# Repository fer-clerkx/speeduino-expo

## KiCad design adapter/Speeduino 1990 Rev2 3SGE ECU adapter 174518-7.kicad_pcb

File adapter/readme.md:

64 pin for NA Toyota MR2 SW20 (1992)

# [For sale here](https://www.tindie.com/products/russian/ecu-64p-connector-bare-pcb-honda-miata-nanb1/)

[Forum thread](https://rusefi.com/forum/viewtopic.php?f=4&t=507)

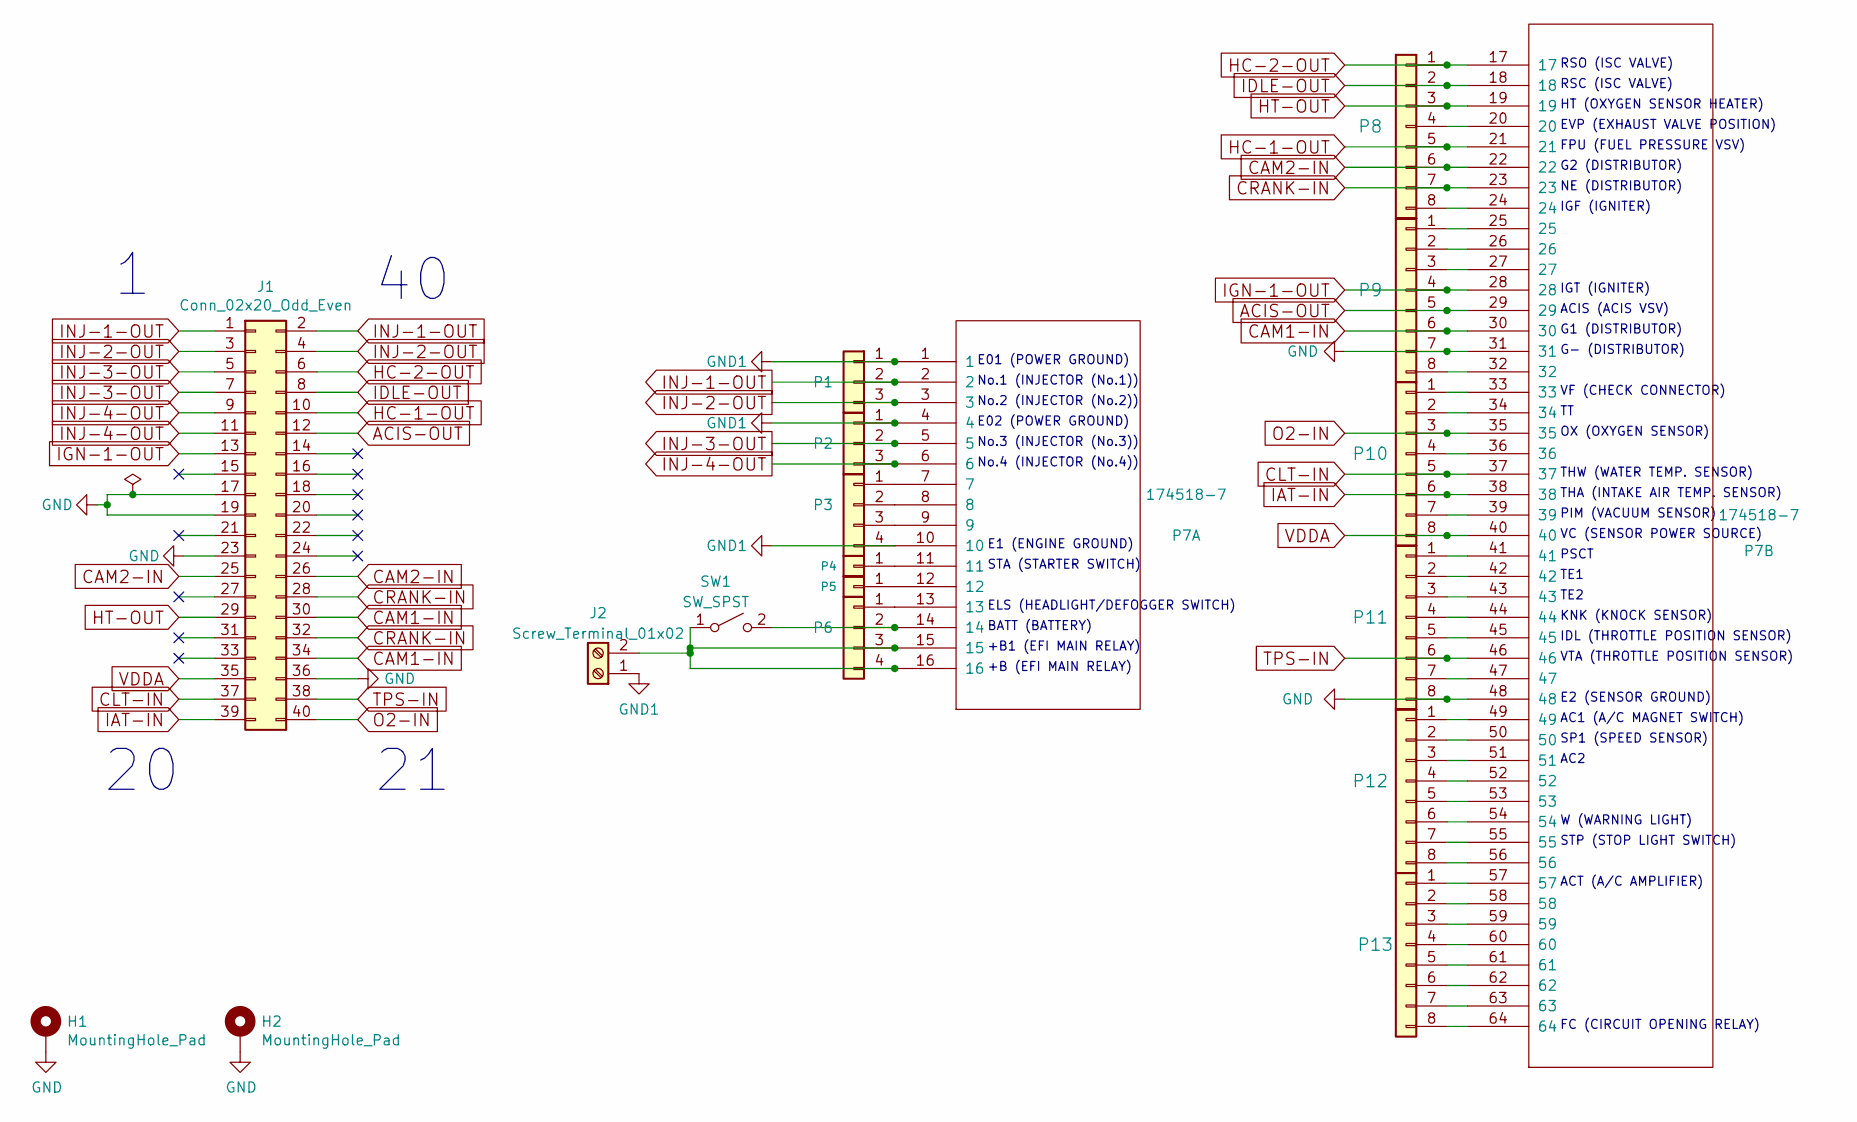
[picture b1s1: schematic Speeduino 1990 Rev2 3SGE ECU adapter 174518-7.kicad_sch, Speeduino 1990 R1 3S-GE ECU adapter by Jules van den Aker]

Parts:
H1, H2: MountingHole_Pad; MountingHole_3.2mm_M3_Pad_Via
J1: Conn_02x20_Odd_Even; IDC-Header_2x20_P2.54mm_Vertical
J2: Screw_Terminal_01x02; TerminalBlock_Phoenix_MKDS-1,5-2_1x02_P5.00mm_Horizontal
P1, P2: CONN_3; PinHeader_1x03_P2.54mm_Vertical
P3, P6: Conn_01x04_Male; PinHeader_2x02_P2.54mm_Vertical
P4, P5: CONN_1; PinHeader_1x01_P2.54mm_Vertical
P7: 174518-7
P8, P9, P10, P11, P12, P13: CONN_8; PinHeader_1x08_P2.54mm_Vertical
SW1: SW_SPST; SolderJumper-2_P1.3mm_Bridged_Pad1.0x1.5mm

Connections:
ACIS-OUT: J1.12, P7.29, P9.5
CAM1-IN: J1.30, J1.34, P7.30, P9.6
CAM2-IN: J1.25, J1.26, P7.22, P8.6
CLT-IN: J1.37, P7.37, P10.5
CRANK-IN: J1.28, J1.32, P7.23, P8.7
GND: H1.1, H2.1, J1.17, J1.19, J1.23, J1.36, P7.31, P7.48, P9.7, P11.8
GND1: J2.1, P1.1, P2.1, P3.4, P7.1, P7.4, P7.10
HC-1-OUT: J1.10, P7.21, P8.5
HC-2-OUT: J1.6, P7.17, P8.1
HT-OUT: J1.29, P7.19, P8.3
IAT-IN: J1.39, P7.38, P10.6
IDLE-OUT: J1.8, P7.18, P8.2
IGN-1-OUT: J1.13, P7.28, P9.4
INJ-1-OUT: J1.1, J1.2, P1.2, P7.2
INJ-2-OUT: J1.3, J1.4, P1.3, P7.3
INJ-3-OUT: J1.5, J1.7, P2.2, P7.5
INJ-4-OUT: J1.9, J1.11, P2.3, P7.6
unnamed: J2.2, P6.3, P6.4, P7.15, P7.16, SW1.1 (A)
unnamed: P3.1, P7.7
unnamed: P3.2, P7.8
unnamed: P3.3, P7.9
unnamed: P4.1, P7.11
unnamed: P5.1, P7.12
unnamed: P6.1, P7.13
unnamed: P6.2, P7.14, SW1.2 (B)
unnamed: P7.20, P8.4
unnamed: P7.24, P8.8
unnamed: P7.25, P9.1
unnamed: P7.26, P9.2
unnamed: P7.27, P9.3
unnamed: P7.32, P9.8
unnamed: P7.33, P10.1
unnamed: P7.34, P10.2
unnamed: P7.36, P10.4
unnamed: P7.39, P10.7
unnamed: P7.41, P11.1
unnamed: P7.42, P11.2
unnamed: P7.43, P11.3
unnamed: P7.44, P11.4
unnamed: P7.45, P11.5
unnamed: P7.47, P11.7
unnamed: P7.49, P12.1
unnamed: P7.50, P12.2
unnamed: P7.51, P12.3
unnamed: P7.52, P12.4
unnamed: P7.53, P12.5
unnamed: P7.54, P12.6
unnamed: P7.55, P12.7
unnamed: P7.56, P12.8
unnamed: P7.57, P13.1
unnamed: P7.58, P13.2
unnamed: P7.59, P13.3
unnamed: P7.60, P13.4
unnamed: P7.61, P13.5
unnamed: P7.62, P13.6
unnamed: P7.63, P13.7
unnamed: P7.64, P13.8
O2-IN: J1.40, P7.35, P10.3
TPS-IN: J1.38, P7.46, P11.6
VDDA: J1.35, P7.40, P10.8

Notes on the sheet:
IGT (IGNITER)
W (WARNING LIGHT)
E02 (POWER GROUND)
No.4 (INJECTOR (No.4))
G1 (DISTRIBUTOR)
No.2 (INJECTOR (No.2))
KNK (KNOCK SENSOR)
NE (DISTRIBUTOR)
STA (STARTER SWITCH)
FPU (FUEL PRESSURE VSV)
AC2
ACT (A/C AMPLIFIER)
+B1 (EFI MAIN RELAY)
RSO (ISC VALVE)
ELS (HEADLIGHT/DEFOGGER SWITCH)
G- (DISTRIBUTOR)
THA (INTAKE AIR TEMP. SENSOR)
No.3 (INJECTOR (No.3))
TE2
RSC (ISC VALVE)
VF (CHECK CONNECTOR)
HT (OXYGEN SENSOR HEATER)
TE1
THW (WATER TEMP. SENSOR)
+B (EFI MAIN RELAY)
E01 (POWER GROUND)
IGF (IGNITER)
OX (OXYGEN SENSOR)
G2 (DISTRIBUTOR)
No.1 (INJECTOR (No.1))
PSCT
FC (CIRCUIT OPENING RELAY)
VTA (THROTTLE POSITION SENSOR)
E2 (SENSOR GROUND)
VC (SENSOR POWER SOURCE)
SP1 (SPEED SENSOR)
ACIS (ACIS VSV)
AC1 (A/C MAGNET SWITCH)
IDL (THROTTLE POSITION SENSOR)
STP (STOP LIGHT SWITCH)

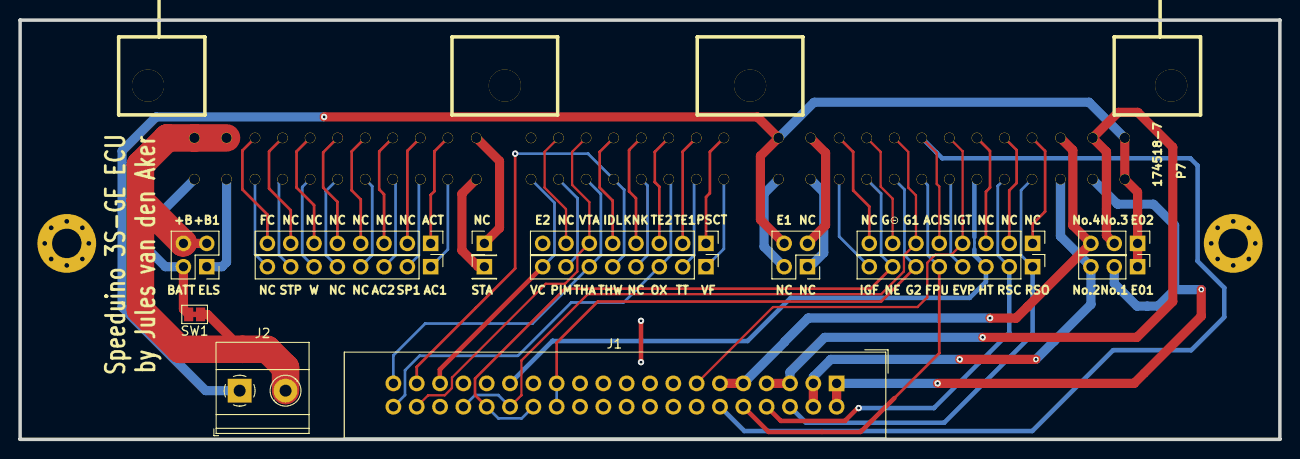
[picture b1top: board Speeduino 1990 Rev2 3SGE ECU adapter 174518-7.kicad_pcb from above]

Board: 2 copper layers, 137.2 x 45.6 mm, 18 parts (0 on the bottom side), 60 nets.

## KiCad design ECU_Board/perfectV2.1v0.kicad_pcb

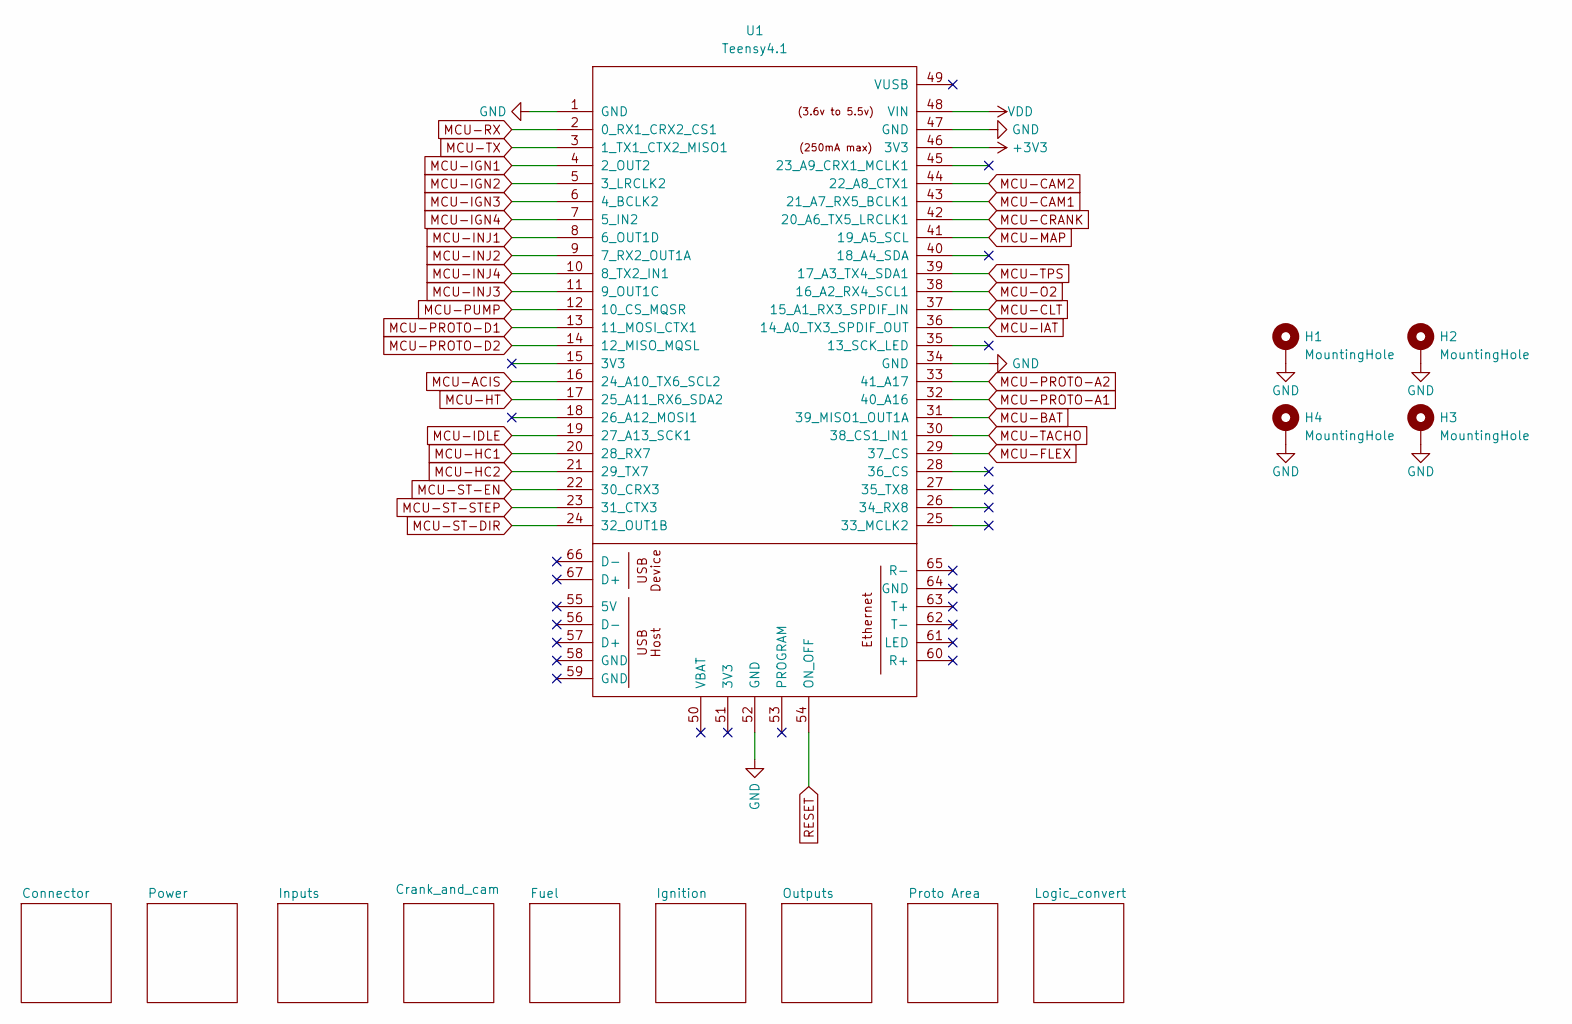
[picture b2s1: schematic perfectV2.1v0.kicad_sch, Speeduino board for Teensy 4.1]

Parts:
H1, H2, H3, H4: MountingHole; MountingHole_4.3mm_M4_Pad
U1: Teensy4.1; Teensy41

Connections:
+3V3: U1.46 (3V3); also elsewhere on the board
GND: H1.1, H2.1, H3.1, H4.1, U1.1 (GND), U1.34 (GND), U1.47 (GND), U1.52 (GND); also elsewhere on the board
MCU-ACIS: U1.16 (24_A10_TX6_SCL2); also elsewhere on the board
MCU-BAT: U1.31 (39_MISO1_OUT1A); also elsewhere on the board
MCU-CAM1: U1.43 (21_A7_RX5_BCLK1); also elsewhere on the board
MCU-CAM2: U1.44 (22_A8_CTX1); also elsewhere on the board
MCU-CLT: U1.37 (15_A1_RX3_SPDIF_IN); also elsewhere on the board
MCU-CRANK: U1.42 (20_A6_TX5_LRCLK1); also elsewhere on the board
MCU-FLEX: U1.29 (37_CS); also elsewhere on the board
MCU-HC1: U1.20 (28_RX7); also elsewhere on the board
MCU-HC2: U1.21 (29_TX7); also elsewhere on the board
MCU-HT: U1.17 (25_A11_RX6_SDA2); also elsewhere on the board
MCU-IAT: U1.36 (14_A0_TX3_SPDIF_OUT); also elsewhere on the board
MCU-IDLE: U1.19 (27_A13_SCK1); also elsewhere on the board
MCU-IGN1: U1.4 (2_OUT2); also elsewhere on the board
MCU-IGN2: U1.5 (3_LRCLK2); also elsewhere on the board
MCU-IGN3: U1.6 (4_BCLK2); also elsewhere on the board
MCU-IGN4: U1.7 (5_IN2); also elsewhere on the board
MCU-INJ1: U1.8 (6_OUT1D); also elsewhere on the board
MCU-INJ2: U1.9 (7_RX2_OUT1A); also elsewhere on the board
MCU-INJ3: U1.11 (9_OUT1C); also elsewhere on the board
MCU-INJ4: U1.10 (8_TX2_IN1); also elsewhere on the board
MCU-MAP: U1.41 (19_A5_SCL); also elsewhere on the board
MCU-O2: U1.38 (16_A2_RX4_SCL1); also elsewhere on the board
MCU-PROTO-A1: U1.32 (40_A16); also elsewhere on the board
MCU-PROTO-A2: U1.33 (41_A17); also elsewhere on the board
MCU-PROTO-D1: U1.13 (11_MOSI_CTX1); also elsewhere on the board
MCU-PROTO-D2: U1.14 (12_MISO_MQSL); also elsewhere on the board
MCU-PUMP: U1.12 (10_CS_MQSR); also elsewhere on the board
MCU-RX: U1.2 (0_RX1_CRX2_CS1); also elsewhere on the board
MCU-ST-DIR: U1.24 (32_OUT1B); also elsewhere on the board
MCU-ST-EN: U1.22 (30_CRX3); also elsewhere on the board
MCU-ST-STEP: U1.23 (31_CTX3); also elsewhere on the board
MCU-TACHO: U1.30 (38_CS1_IN1); also elsewhere on the board
MCU-TPS: U1.39 (17_A3_TX4_SDA1); also elsewhere on the board
MCU-TX: U1.3 (1_TX1_CTX2_MISO1); also elsewhere on the board
RESET: U1.54 (ON_OFF); also elsewhere on the board
VDD: U1.48 (VIN); also elsewhere on the board

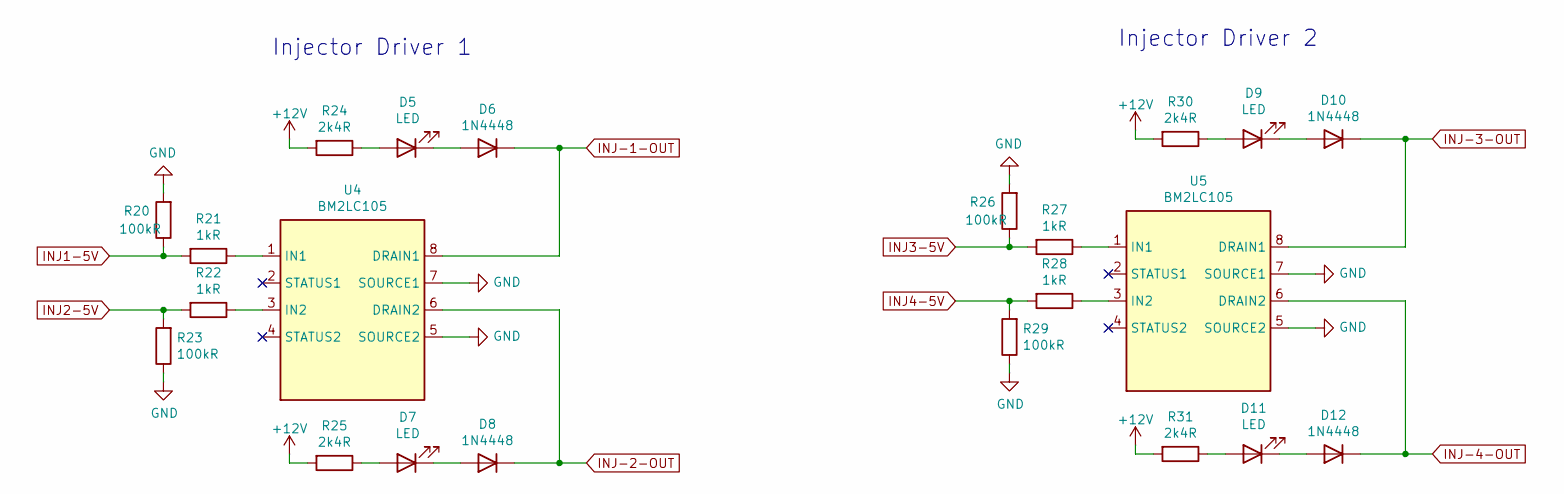
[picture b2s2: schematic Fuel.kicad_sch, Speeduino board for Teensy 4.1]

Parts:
D5, D7, D9, D11: LED; LED_0805_2012Metric; Manufacturer_Part_Number MP008293; Digikey Part Number 3796325
D6, D8, D10, D12: 1N4448; D_SOD-123; Manufacturer_Part_Number 1N4448W-7-F; Digikey Part Number 1843738
R20, R23, R26, R29: 100kR; R_0402_1005Metric; Manufacturer_Part_Number WF04P1003FTL; Digikey Part Number 2502803
R21, R22, R27, R28: 1kR; R_0402_1005Metric; Manufacturer_Part_Number WF04P1001FTL; Digikey Part Number 2502798
R24, R25, R30, R31: 2k4R; R_0805_2012Metric; Manufacturer_Part_Number MCWR08X2401FTL; Digikey Part Number 2447625
U4, U5: BM2LC105; SOP-8_3.9x4.9mm_P1.27mm; Manufacturer_Part_Number BM2LC105FJ-CE2; Digikey Part Number BM2LC105FJ-CE2CT-ND

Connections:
+12V: R24.2, R25.2, R30.2, R31.2; also elsewhere on the board
GND: R20.2, R23.1, R26.2, R29.1, U4.5 (SOURCE2), U4.7 (SOURCE1), U5.5 (SOURCE2), U5.7 (SOURCE1); also elsewhere on the board
INJ1-5V: R20.1, R21.2; also elsewhere on the board
INJ2-5V: R22.2, R23.2; also elsewhere on the board
INJ3-5V: R26.1, R27.2; also elsewhere on the board
INJ4-5V: R28.2, R29.2; also elsewhere on the board
INJ-1-OUT: D6.1 (K), U4.8 (DRAIN1); also elsewhere on the board
INJ-2-OUT: D8.1 (K), U4.6 (DRAIN2); also elsewhere on the board
INJ-3-OUT: D10.1 (K), U5.8 (DRAIN1); also elsewhere on the board
INJ-4-OUT: D12.1 (K), U5.6 (DRAIN2); also elsewhere on the board
unnamed: D5.1 (K), D6.2 (A)
unnamed: D5.2 (A), R24.1
unnamed: D7.1 (K), D8.2 (A)
unnamed: D7.2 (A), R25.1
unnamed: D9.2 (A), R30.1
unnamed: D9.1 (K), D10.2 (A)
unnamed: D11.1 (K), D12.2 (A)
unnamed: D11.2 (A), R31.1
unnamed: R21.1, U4.1 (IN1)
unnamed: R22.1, U4.3 (IN2)
unnamed: R27.1, U5.1 (IN1)
unnamed: R28.1, U5.3 (IN2)

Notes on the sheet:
Injector Driver 2
Injector Driver 1

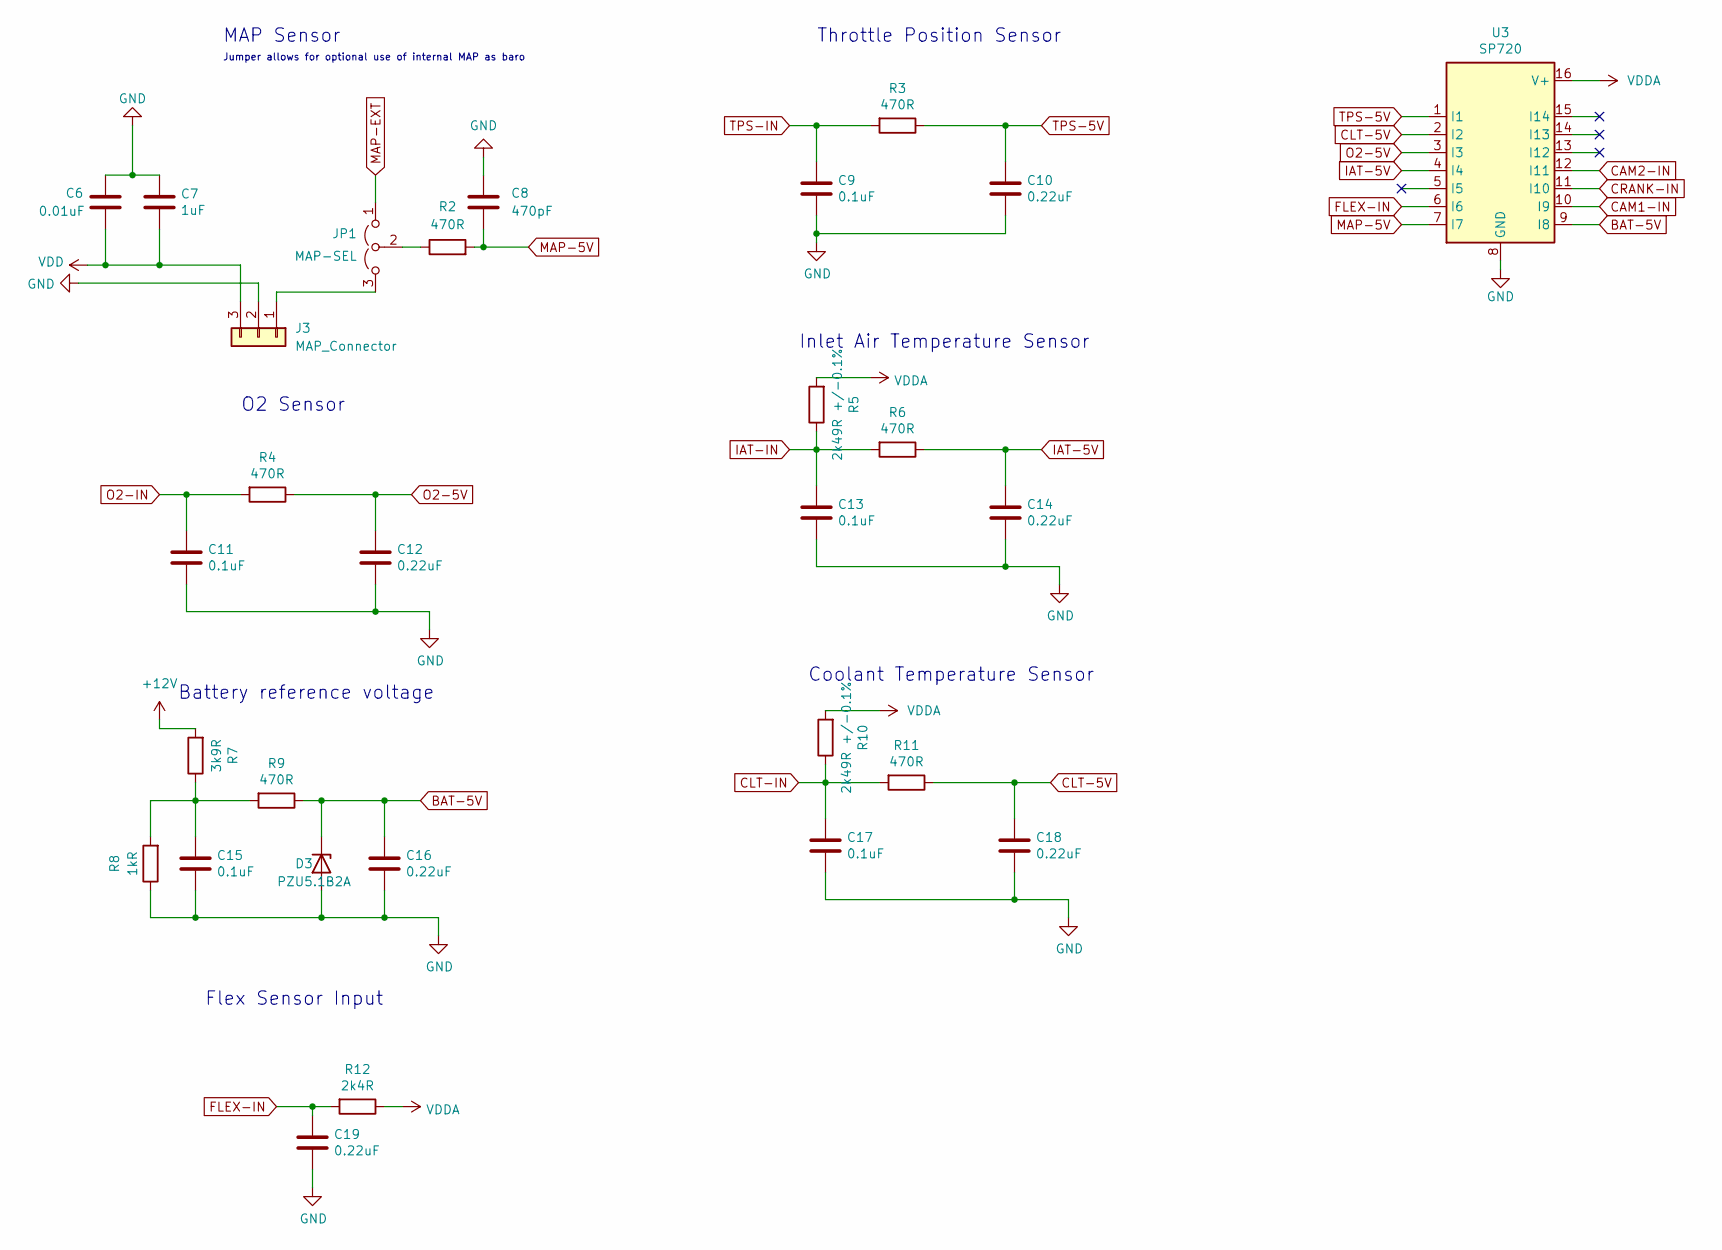
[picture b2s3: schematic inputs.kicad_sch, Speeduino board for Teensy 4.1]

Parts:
C6: 0.01uF; C_0805_2012Metric; Manufacturer_Part_Number CC0805KRX7R9BB103; Digikey Part Number 3019937
C7: 1uF; C_0805_2012Metric; Manufacturer_Part_Number CC0805KKX7R7BB105; Digikey Part Number 3369302
C8: 470pF; C_0805_2012Metric; Manufacturer_Part_Number MC0805B471K500CT; Digikey Part Number 1759216
C9, C11, C13, C15, C17: 0.1uF; C_0805_2012Metric; Manufacturer_Part_Number VJ0805Y104KXAPW1BC; Digikey Part Number 3296136
C10, C12, C14, C16, C18, C19: 0.22uF; C_0805_2012Metric; Manufacturer_Part_Number 0805B224M160CP; Digikey Part Number 3881054
D3: PZU5.1B2A; D_SOD-323; Manufacturer_Part_Number PZU5.1B2A-QX; Digikey Part Number 4126444
J3: MAP_Connector; PinSocket_1x03_P2.54mm_Vertical
JP1: MAP-SEL; PinHeader_1x03_P2.54mm_Vertical
R2, R3, R4, R6, R9, R11: 470R; R_0805_2012Metric; Manufacturer_Part_Number WF08P4700FTL; Digikey Part Number 2670094
R5, R10: 2k49R +/-0.1%; R_0805_2012Metric; Manufacturer_Part_Number RT0805BRD072K49L; Digikey Part Number 4014068
R7: 3k9R; R_0805_2012Metric; Manufacturer_Part_Number MCWR08X3901FTL; Digikey Part Number 2447654
R8: 1kR; R_0402_1005Metric; Manufacturer_Part_Number WF04P1001FTL; Digikey Part Number 2502798
R12: 2k4R; R_0805_2012Metric; Manufacturer_Part_Number MCWR08X2401FTL; Digikey Part Number 2447625
U3: SP720; SOIC-16_3.9x9.9mm_P1.27mm; Manufacturer_Part_Number SP720ABG; Digikey Part Number 1869378

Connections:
+12V: R7.2; also elsewhere on the board
BAT-5V: C16.1, D3.1 (K), R9.1, U3.9 (I8); also elsewhere on the board
CAM1-IN: U3.10 (I9); also elsewhere on the board
CAM2-IN: U3.12 (I11); also elsewhere on the board
CLT-5V: C18.1, R11.1, U3.2 (I2); also elsewhere on the board
CLT-IN: C17.1, R10.1, R11.2; also elsewhere on the board
CRANK-IN: U3.11 (I10); also elsewhere on the board
FLEX-IN: C19.1, R12.2, U3.6 (I6); also elsewhere on the board
GND: C6.1, C7.1, C8.1, C9.2, C10.2, C11.2, C12.2, C13.2, C14.2, C15.2, C16.2, C17.2, C18.2, C19.2, D3.2 (A), J3.2, R8.1, U3.8 (GND); also elsewhere on the board
IAT-5V: C14.1, R6.1, U3.4 (I4); also elsewhere on the board
IAT-IN: C13.1, R5.1, R6.2; also elsewhere on the board
MAP-5V: C8.2, R2.2, U3.7 (I7); also elsewhere on the board
MAP-EXT: JP1.1 (A); also elsewhere on the board
unnamed: C15.1, R7.1, R8.2, R9.2
unnamed: J3.1, JP1.3 (B)
unnamed: JP1.2 (C), R2.1
O2-5V: C12.1, R4.1, U3.3 (I3); also elsewhere on the board
O2-IN: C11.1, R4.2; also elsewhere on the board
TPS-5V: C10.1, R3.1, U3.1 (I1); also elsewhere on the board
TPS-IN: C9.1, R3.2; also elsewhere on the board
VDD: C6.2, C7.2, J3.3; also elsewhere on the board
VDDA: R5.2, R10.2, R12.1, U3.16 (V+); also elsewhere on the board

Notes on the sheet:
Coolant Temperature Sensor
Battery reference voltage
Inlet Air Temperature Sensor
Flex Sensor Input
O2 Sensor
Jumper allows for optional use of internal MAP as baro
Throttle Position Sensor
MAP Sensor

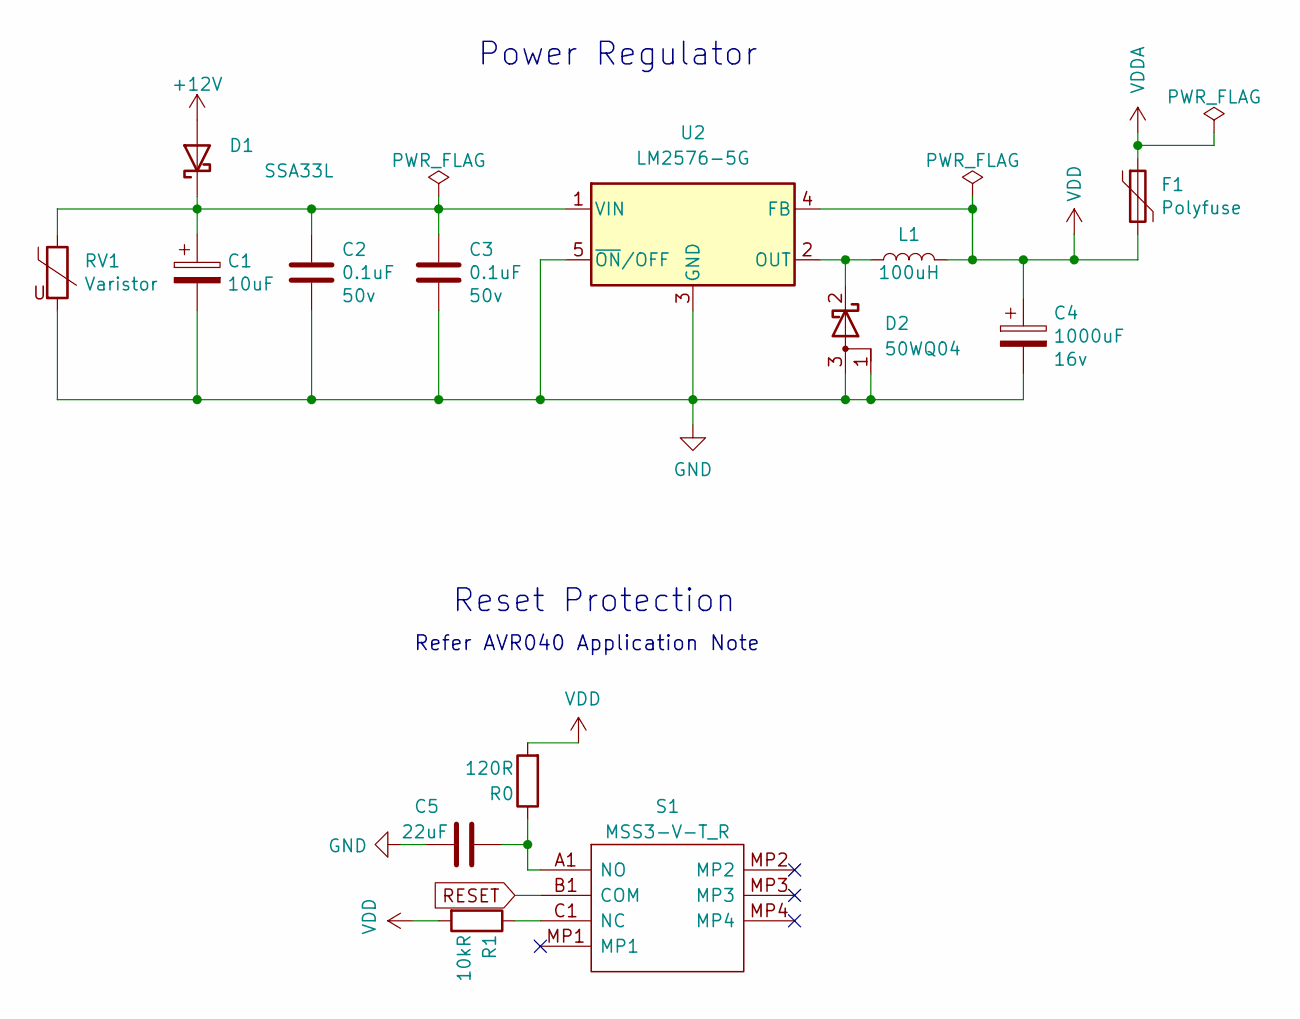
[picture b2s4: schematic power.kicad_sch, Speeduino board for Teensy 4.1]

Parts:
C1: 10uF; CP_EIA-7343-31_Kemet-D; Voltage 35v; Manufacturer_Part_Number TAJD106K050RNJ; Digikey Part Number 1432387
C2, C3: 0.1uF; C_0805_2012Metric; Voltage 50v; Manufacturer_Part_Number VJ0805Y104KXAPW1BC; Digikey Part Number 3296136
C4: 1000uF; CP_Elec_16x17.5; Voltage 16v; Manufacturer_Part_Number MCVZH050M102JB7L; Digikey Part Number 2630479
C5: 22uF; C_0805_2012Metric; Manufacturer_Part_Number GRM21BR61A226ME51K; Digikey Part Number 3581408
D1: SSA33L; D_SMA; Manufacturer_Part_Number SSA33L-E3/61T; Digikey Part Number 1336552
D2: 50WQ04; TO-252-3_TabPin4; Manufacturer_Part_Number VS-50WQ04FNTR-M3; Digikey Part Number 2646457
F1: Polyfuse; Fuse_1812_4532Metric; Manufacturer_Part_Number SMD1812B050TF/30; Digikey Part Number 3052512
L1: 100uH; L_12x12mm_H8mm; Manufacturer_Part_Number MSS1210-104KED; Digikey Part Number 2288307
R0: 120R; R_0603_1608Metric; Manufacturer_Part_Number WF06P1200FTL; Digikey Part Number 2670000
R1: 10kR; R_0805_2012Metric; Manufacturer_Part_Number CRG0805F10K/10; Digikey Part Number 3399587
RV1: Varistor; C_2220_5650Metric; Manufacturer_Part_Number VC2220K122R014; Digikey Part Number 2989479
S1: MSS3-V-T_R; MSS3VTR; Manufacturer_Part_Number MSS3-V-T/R; Digikey Part Number 2113262
U2: LM2576-5G; TO-263-5_TabPin6; Manufacturer_Part_Number LM2576D2TR4-5G; Digikey Part Number 2534166

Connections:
+12V: D1.2 (A); also elsewhere on the board
GND: C1.2, C2.2, C3.2, C4.2, C5.2, D2.1 (A), D2.3 (A), RV1.2, U2.3 (GND), U2.5 (~ON/OFF); also elsewhere on the board
unnamed: C1.1, C2.1, C3.1, D1.1 (K), RV1.1, U2.1 (VIN)
unnamed: C5.1, R0.1, S1.A1 (NO)
unnamed: D2.2 (K), L1.1, U2.2 (OUT)
unnamed: R1.1, S1.C1 (NC)
RESET: S1.B1 (COM); also elsewhere on the board
VDD: C4.1, F1.2, L1.2, R0.2, R1.2, U2.4 (FB); also elsewhere on the board
VDDA: F1.1; also elsewhere on the board

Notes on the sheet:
Power Regulator
Reset Protection
Refer AVR040 Application Note

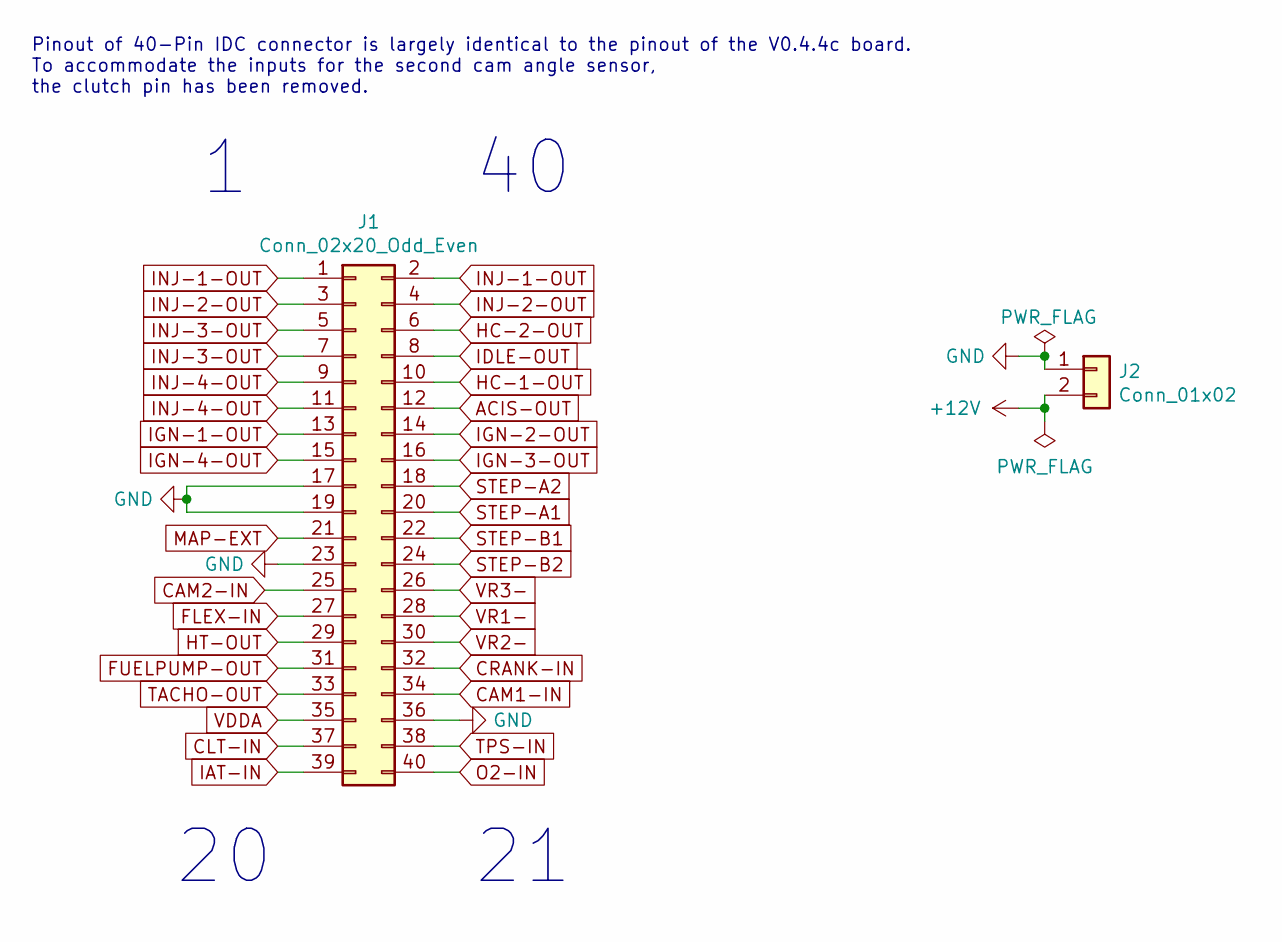
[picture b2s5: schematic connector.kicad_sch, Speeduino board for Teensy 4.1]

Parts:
J1: Conn_02x20_Odd_Even; IDC-Header_2x20_P2.54mm_Vertical
J2: Conn_01x02; TerminalBlock_Phoenix_MKDS-1,5-2-5.08_1x02_P5.08mm_Horizont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; Manufacturer_Part_Number PM5.08/2/90 BLK

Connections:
+12V: J2.2; also elsewhere on the board
ACIS-OUT: J1.12; also elsewhere on the board
CAM1-IN: J1.34; also elsewhere on the board
CAM2-IN: J1.25; also elsewhere on the board
CLT-IN: J1.37; also elsewhere on the board
CRANK-IN: J1.32; also elsewhere on the board
FLEX-IN: J1.27; also elsewhere on the board
FUELPUMP-OUT: J1.31; also elsewhere on the board
GND: J1.17, J1.19, J1.23, J1.36, J2.1; also elsewhere on the board
HC-1-OUT: J1.10; also elsewhere on the board
HC-2-OUT: J1.6; also elsewhere on the board
HT-OUT: J1.29; also elsewhere on the board
IAT-IN: J1.39; also elsewhere on the board
IDLE-OUT: J1.8; also elsewhere on the board
IGN-1-OUT: J1.13; also elsewhere on the board
IGN-2-OUT: J1.14; also elsewhere on the board
IGN-3-OUT: J1.16; also elsewhere on the board
IGN-4-OUT: J1.15; also elsewhere on the board
INJ-1-OUT: J1.1, J1.2; also elsewhere on the board
INJ-2-OUT: J1.3, J1.4; also elsewhere on the board
INJ-3-OUT: J1.5, J1.7; also elsewhere on the board
INJ-4-OUT: J1.9, J1.11; also elsewhere on the board
MAP-EXT: J1.21; also elsewhere on the board
O2-IN: J1.40; also elsewhere on the board
STEP-A1: J1.20; also elsewhere on the board
STEP-A2: J1.18; also elsewhere on the board
STEP-B1: J1.22; also elsewhere on the board
STEP-B2: J1.24; also elsewhere on the board
TACHO-OUT: J1.33; also elsewhere on the board
TPS-IN: J1.38; also elsewhere on the board
VDDA: J1.35; also elsewhere on the board
VR1-: J1.28; also elsewhere on the board
VR2-: J1.30; also elsewhere on the board
VR3-: J1.26; also elsewhere on the board

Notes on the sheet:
Pinout of 40-Pin IDC connector is largely identical to the pinout of the V0.4.4c board. To accommodate the inputs for the second cam angle sensor, the clutch pin has been removed.

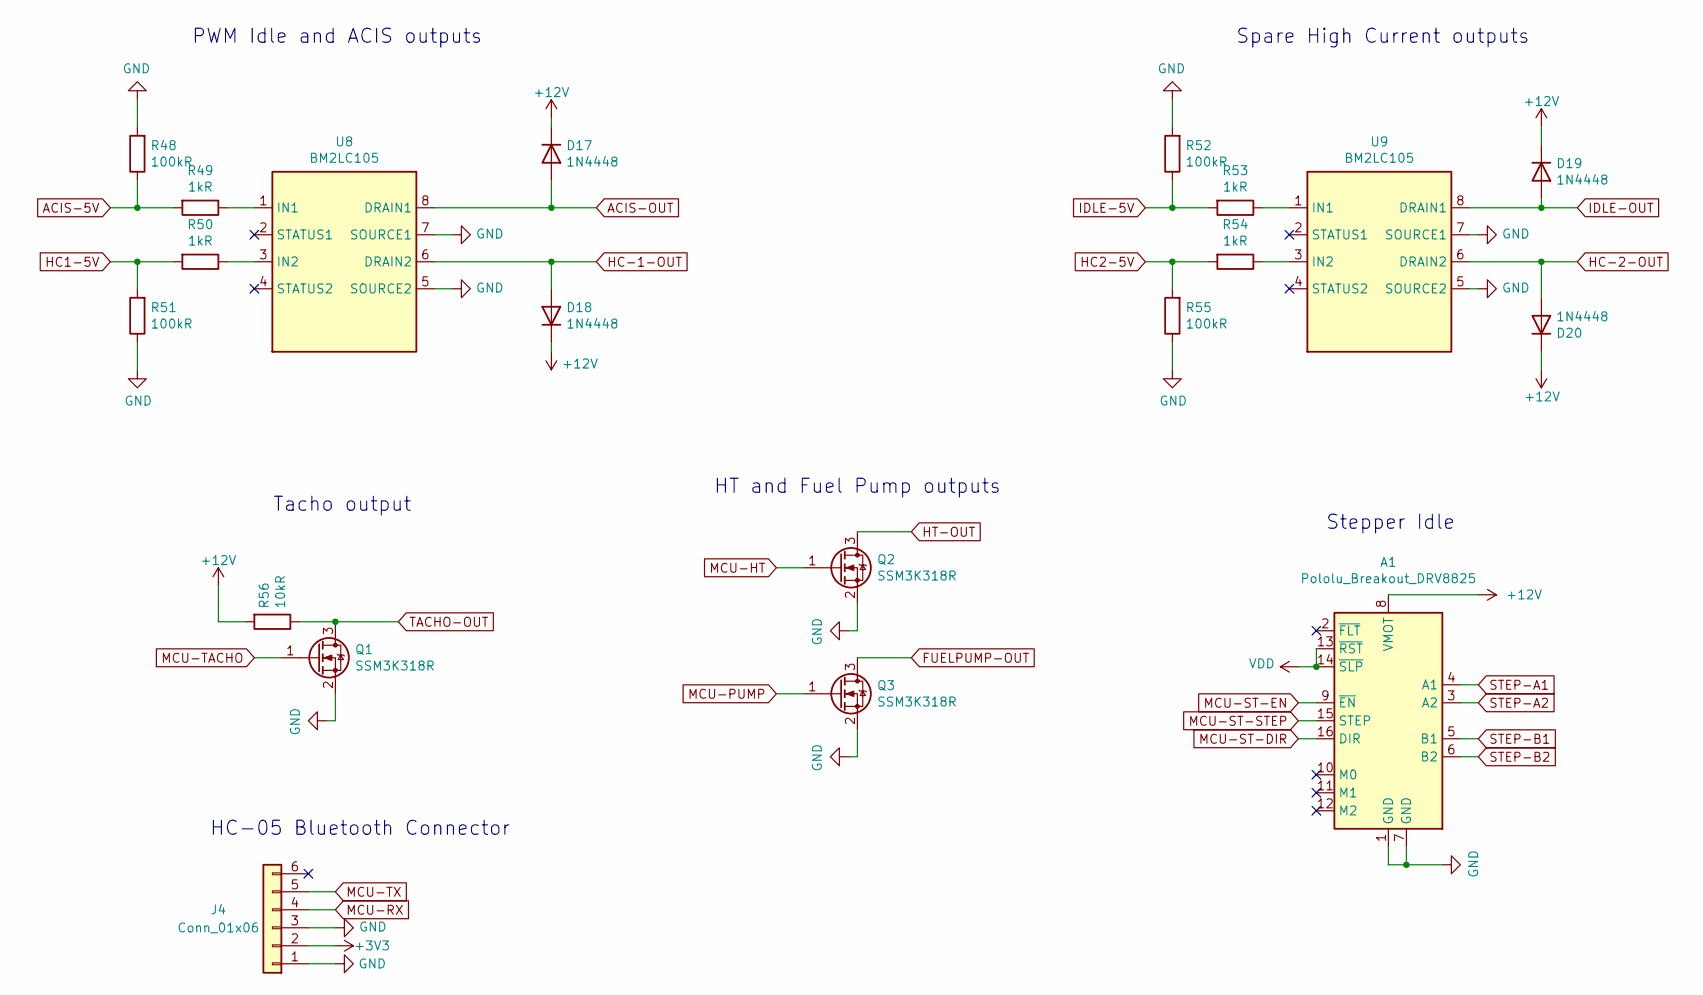
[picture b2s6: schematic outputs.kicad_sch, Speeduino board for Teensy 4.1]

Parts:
A1: Pololu_Breakout_DRV8825; Pololu_Breakout-16_15.2x20.3mm
D17, D18, D19, D20: 1N4448; D_SOD-123; Manufacturer_Part_Number 1N4448W-7-F; Digikey Part Number 1843738
J4: Conn_01x06; PinHeader_1x06_P2.54mm_Vertical
Q1, Q2, Q3: SSM3K318R; SOT-23; Manufacturer_Part_Number SSM3K318R; Digikey Part Number 3870097
R48, R51, R52, R55: 100kR; R_0402_1005Metric; Manufacturer_Part_Number WF04P1003FTL; Digikey Part Number 2502803
R49, R50, R53, R54: 1kR; R_0402_1005Metric; Manufacturer_Part_Number WF04P1001FTL; Digikey Part Number 2502798
R56: 10kR; R_0805_2012Metric; Manufacturer_Part_Number CRG0805F10K/10; Digikey Part Number 3399587
U8, U9: BM2LC105; SOP-8_3.9x4.9mm_P1.27mm; Manufacturer_Part_Number BM2LC105FJ-CE2; Digikey Part Number BM2LC105FJ-CE2CT-ND

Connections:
+3V3: J4.2; also elsewhere on the board
+12V: A1.8 (VMOT), D17.1 (K), D18.1 (K), D19.1 (K), D20.1 (K), R56.2; also elsewhere on the board
ACIS-5V: R48.1, R49.2; also elsewhere on the board
ACIS-OUT: D17.2 (A), U8.8 (DRAIN1); also elsewhere on the board
FUELPUMP-OUT: Q3.3 (D); also elsewhere on the board
GND: A1.1 (GND), A1.7 (GND), J4.1, J4.3, Q1.2 (S), Q2.2 (S), Q3.2 (S), R48.2, R51.1, R52.2, R55.1, U8.5 (SOURCE2), U8.7 (SOURCE1), U9.5 (SOURCE2), U9.7 (SOURCE1); also elsewhere on the board
HC1-5V: R50.2, R51.2; also elsewhere on the board
HC2-5V: R54.2, R55.2; also elsewhere on the board
HC-1-OUT: D18.2 (A), U8.6 (DRAIN2); also elsewhere on the board
HC-2-OUT: D20.2 (A), U9.6 (DRAIN2); also elsewhere on the board
HT-OUT: Q2.3 (D); also elsewhere on the board
IDLE-5V: R52.1, R53.2; also elsewhere on the board
IDLE-OUT: D19.2 (A), U9.8 (DRAIN1); also elsewhere on the board
MCU-HT: Q2.1 (G); also elsewhere on the board
MCU-PUMP: Q3.1 (G); also elsewhere on the board
MCU-RX: J4.4; also elsewhere on the board
MCU-ST-DIR: A1.16 (DIR); also elsewhere on the board
MCU-ST-EN: A1.9 (~EN); also elsewhere on the board
MCU-ST-STEP: A1.15 (STEP); also elsewhere on the board
MCU-TACHO: Q1.1 (G); also elsewhere on the board
MCU-TX: J4.5; also elsewhere on the board
unnamed: R49.1, U8.1 (IN1)
unnamed: R50.1, U8.3 (IN2)
unnamed: R53.1, U9.1 (IN1)
unnamed: R54.1, U9.3 (IN2)
STEP-A1: A1.4 (A1); also elsewhere on the board
STEP-A2: A1.3 (A2); also elsewhere on the board
STEP-B1: A1.5 (B1); also elsewhere on the board
STEP-B2: A1.6 (B2); also elsewhere on the board
TACHO-OUT: Q1.3 (D), R56.1; also elsewhere on the board
VDD: A1.13 (~RST), A1.14 (~SLP); also elsewhere on the board

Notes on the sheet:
HT and Fuel Pump outputs
Stepper Idle
PWM Idle and ACIS outputs
HC-05 Bluetooth Connector
Tacho output
Spare High Current outputs

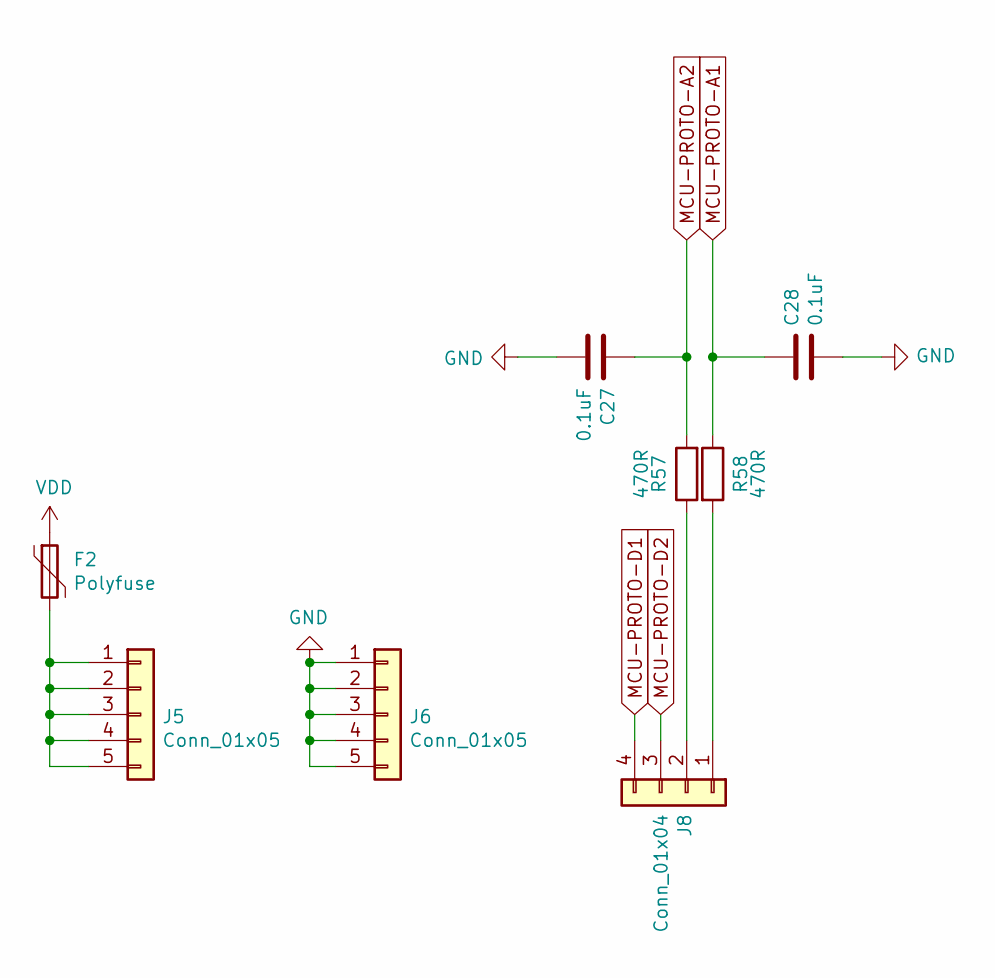
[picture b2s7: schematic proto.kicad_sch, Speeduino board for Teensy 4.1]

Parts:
C27, C28: 0.1uF; C_0805_2012Metric; Manufacturer_Part_Number VJ0805Y104KXAPW1BC; Digikey Part Number 3296136
F2: Polyfuse; Fuse_1812_4532Metric; Manufacturer_Part_Number SMD1812B050TF/30; Digikey Part Number 3052512
J5, J6: Conn_01x05; PinHeader_1x05_P2.54mm_Vertical
J8: Conn_01x04; PinHeader_1x04_P2.54mm_Vertical
R57, R58: 470R; R_0805_2012Metric; Manufacturer_Part_Number WF08P4700FTL; Digikey Part Number 2670094

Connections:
GND: C27.2, C28.2, J6.1, J6.2, J6.3, J6.4, J6.5; also elsewhere on the board
MCU-PROTO-A1: C28.1, R57.1; also elsewhere on the board
MCU-PROTO-A2: C27.1, R58.2; also elsewhere on the board
MCU-PROTO-D1: J8.4; also elsewhere on the board
MCU-PROTO-D2: J8.3; also elsewhere on the board
unnamed: F2.2, J5.1, J5.2, J5.3, J5.4, J5.5
unnamed: J8.1, R57.2
unnamed: J8.2, R58.1
VDD: F2.1; also elsewhere on the board
